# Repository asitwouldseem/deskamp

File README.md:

# deskamp
Class D amplifier / ESPHome pre-amp to match the custom speakers.

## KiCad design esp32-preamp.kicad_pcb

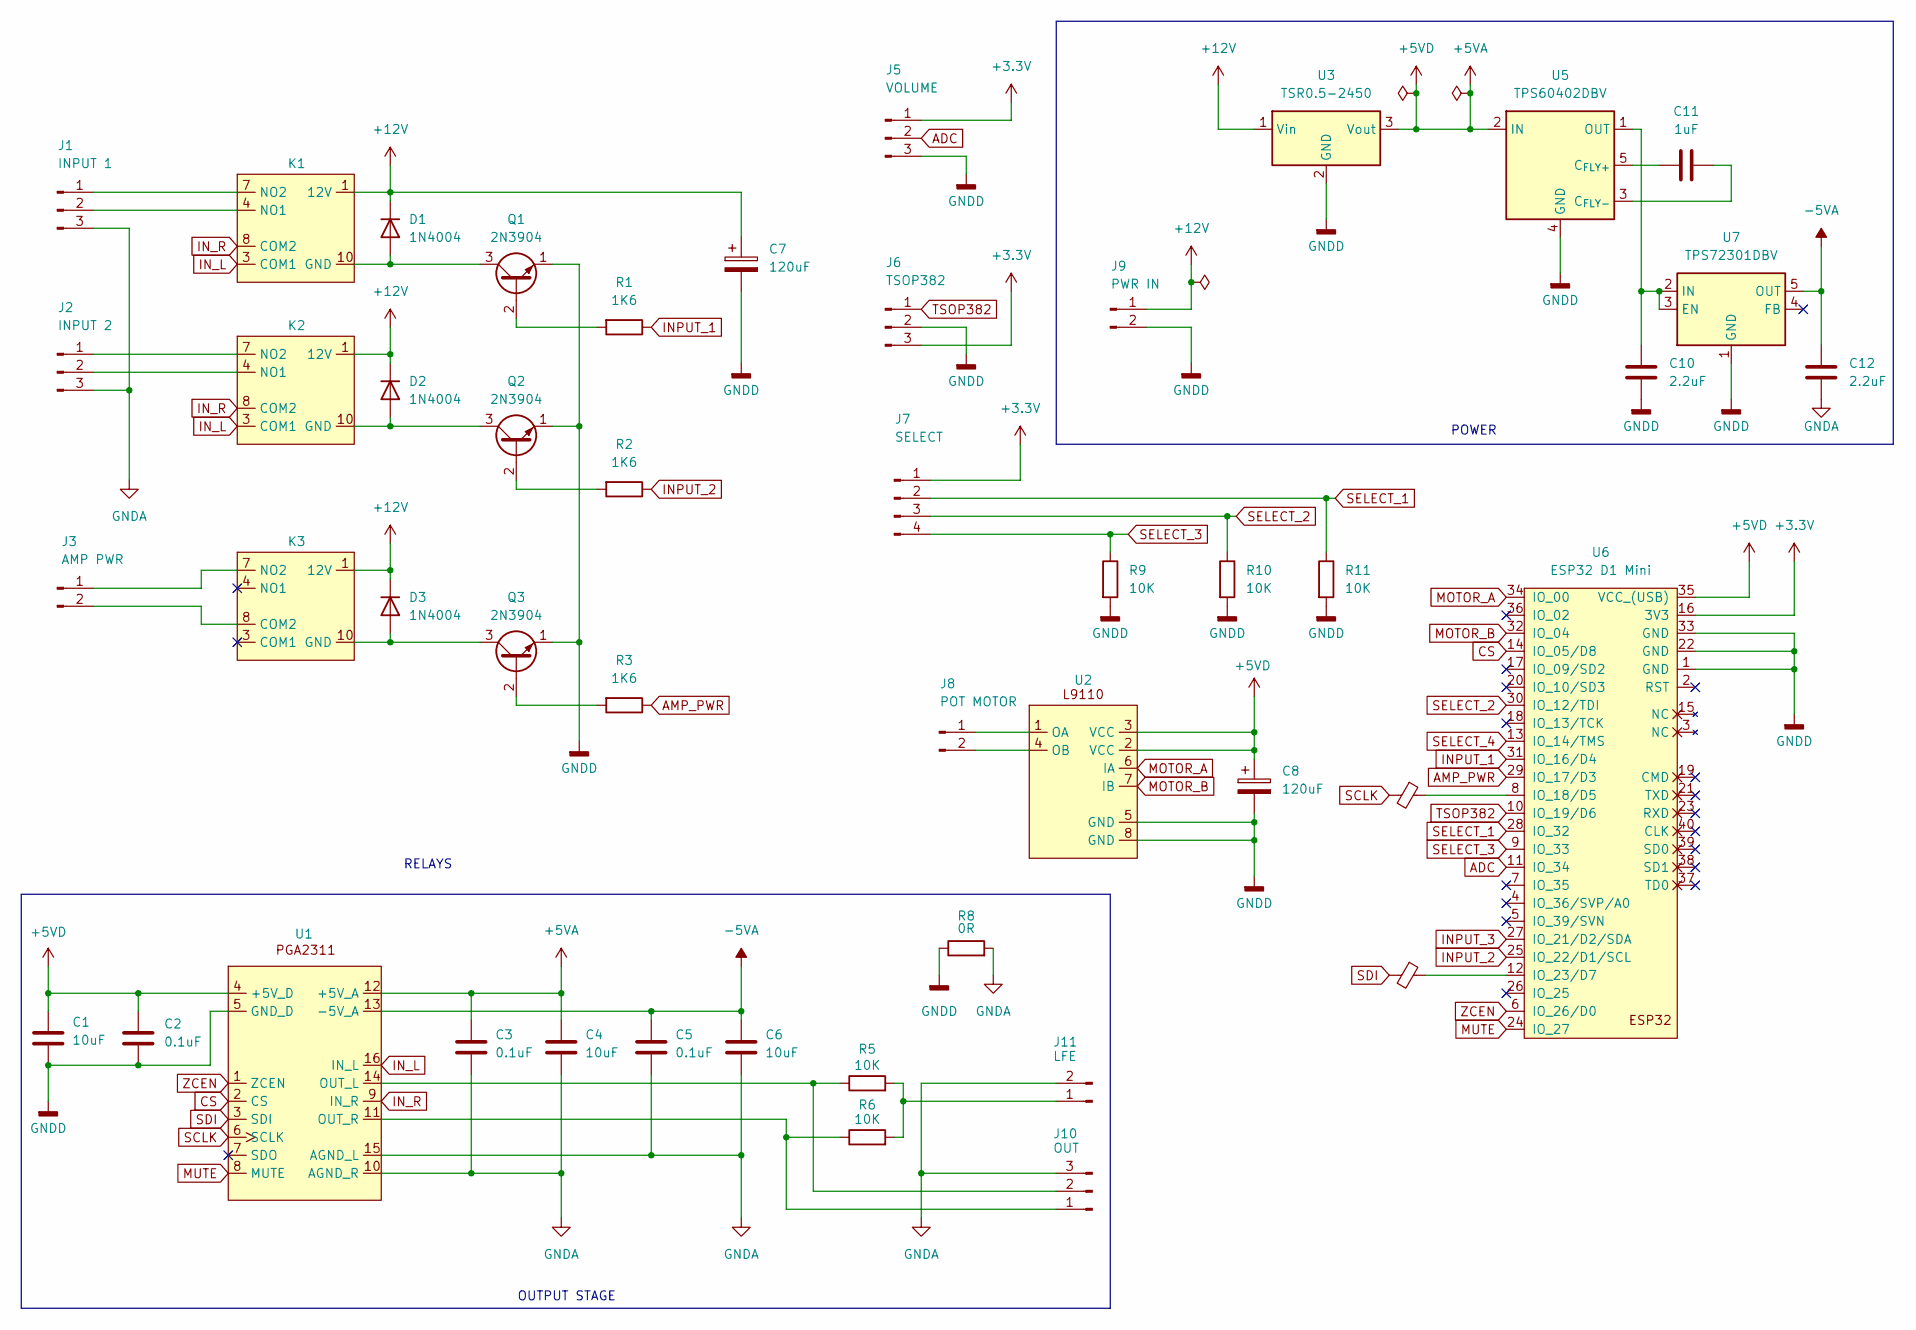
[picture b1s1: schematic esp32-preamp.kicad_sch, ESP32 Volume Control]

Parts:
C1, C4, C6: 10uF; C_Radial_D4.0mm_H5.0mm_P1.50mm
C2, C3, C5: 0.1uF; C_1206_3216Metric_Pad1.33x1.80mm_HandSolder
C7, C8: 120uF; C_Radial_D4.0mm_H5.0mm_P1.50mm
C10, C12: 2.2uF; C_1206_3216Metric_Pad1.33x1.80mm_HandSolder
C11: 1uF; C_1206_3216Metric_Pad1.33x1.80mm_HandSolder
D1, D2, D3: 1N4004; D_DO-41_SOD81_P10.16mm_Horizontal
FB1, FB2: FerriteBead_Small; C_1206_3216Metric_Pad1.33x1.80mm_HandSolder
J1: INPUT 1; JST_XH_B3B-XH-A_1x03_P2.50mm_Vertical
J2: INPUT 2; JST_XH_B3B-XH-A_1x03_P2.50mm_Vertical
J3: AMP PWR; JST_XH_B2B-XH-A_1x02_P2.50mm_Vertical
J5: VOLUME; JST_XH_B3B-XH-A_1x03_P2.50mm_Vertical
J6: TSOP382; JST_XH_B3B-XH-A_1x03_P2.50mm_Vertical
J7: SELECT; JST_XH_B4B-XH-A_1x04_P2.50mm_Vertical
J8: POT MOTOR; JST_XH_B2B-XH-A_1x02_P2.50mm_Vertical
J9: PWR IN; JST_XH_B2B-XH-A_1x02_P2.50mm_Vertical
J10: LFE; JST_XH_B2B-XH-A_1x02_P2.50mm_Vertical
J11: OUT; JST_XH_B3B-XH-A_1x03_P2.50mm_Vertical
K1, K2, K3: RELAY_TQ2_PAN
Q1, Q2, Q3: 2N3904; TO-92_Inline
R1, R2, R3: 1K6; R_1206_3216Metric_Pad1.30x1.75mm_HandSolder
R5, R6: 10K; R_Axial_Power_L30.0mm_W9.0mm_P36.4mm
R8: 0R; R_1206_3216Metric_Pad1.30x1.75mm_HandSolder
R9, R10, R11: 10K; R_1206_3216Metric_Pad1.30x1.75mm_HandSolder
U1: DW16
U2: DIP-8_W7.62mm_Socket
U3: TSR0.5-2450; Converter_DCDC_TRACO_TSR0.5-24xx_TSR0.5-24xxx_THT
U5: TPS60402DBV; SOT-23-5
U6: ESP32 D1 Mini; esp32-wemos-d1-mini
U7: TPS72301DBV; SOT-23-5

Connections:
+3.3V: J5.1, J6.3, J7.1, U6.16 (3V3)
+5VA: C1.1, C2.1, C3.1, C4.1, C8.1, U1.4 (+5V_D), U1.12 (+5V_A), U2.2 (VCC), U2.3 (VCC), U3.3 (Vout), U5.2 (IN), U6.35 (VCC_(USB))
+12V: C7.1, D1.1 (K), D2.1 (K), D3.1 (K), J9.1, K1.1 (12V), K2.1 (12V), K3.1 (12V), U3.1 (Vin)
-5VA: C5.1, C6.1, C12.1, U1.13 (-5V_A), U7.5 (OUT)
ADC: J5.2, U6.11 (IO_34)
AMP_PWR: R3.1, U6.29 (IO_17/D3)
CS: U1.2 (CS), U6.14 (IO_05/D8)
GNDA: C3.2, C4.2, C5.2, C6.2, C12.2, J1.3, J2.3, J10.2, J11.3, R8.2, U1.10 (AGND_R), U1.15 (AGND_L)
GNDD: C1.2, C2.2, C7.2, C8.2, C10.2, J5.3, J6.2, J9.2, Q1.1 (E), Q2.1 (E), Q3.1 (E), R8.1, R9.2, R10.2, R11.2, U1.5 (GND_D), U2.5 (GND), U2.8 (GND), U3.2 (GND), U5.4 (GND), U6.1 (GND), U6.22 (GND), U6.33 (GND), U7.1 (GND)
INPUT_1: R1.1, U6.31 (IO_16/D4)
INPUT_2: R2.1, U6.25 (IO_22/D1/SCL)
INPUT_3: U6.27 (IO_21/D2/SDA)
IN_L: K1.3 (COM1), K2.3 (COM1), U1.16 (IN_L)
IN_R: K1.8 (COM2), K2.8 (COM2), U1.9 (IN_R)
MOTOR_A: U2.6 (IA), U6.34 (IO_00)
MOTOR_B: U2.7 (IB), U6.32 (IO_04)
MUTE: U1.8 (MUTE), U6.24 (IO_27)
unnamed: D1.2 (A), K1.10 (GND), Q1.3 (C)
unnamed: D2.2 (A), K2.10 (GND), Q2.3 (C)
unnamed: D3.2 (A), K3.10 (GND), Q3.3 (C)
unnamed: J1.1, K1.7 (NO2)
unnamed: J1.2, K1.4 (NO1)
unnamed: J2.1, K2.7 (NO2)
unnamed: J2.2, K2.4 (NO1)
unnamed: J3.1, K3.7 (NO2)
unnamed: J3.2, K3.8 (COM2)
unnamed: J8.1, U2.1 (OA)
unnamed: J8.2, U2.4 (OB)
unnamed: J10.1, R5.2, R6.2
unnamed: J11.1, R6.1, U1.11 (OUT_R)
unnamed: J11.2, R5.1, U1.14 (OUT_L)
unnamed: Q1.2 (B), R1.2
unnamed: Q2.2 (B), R2.2
unnamed: Q3.2 (B), R3.2
unnamed: C11.1, U5.5 (C_{FLY+})
unnamed: C11.2, U5.3 (C_{FLY-})
unnamed: C10.1, U5.1 (OUT), U7.2 (IN), U7.3 (EN)
unnamed: FB1.1, U6.8 (IO_18/D5)
unnamed: FB2.1, U6.12 (IO_23/D7)
SCLK: FB1.2, U1.6 (SCLK)
SDI: FB2.2, U1.3 (SDI)
SELECT_1: J7.2, R11.1, U6.28 (IO_32)
SELECT_2: J7.3, R10.1, U6.30 (IO_12/TDI)
SELECT_3: J7.4, R9.1, U6.9 (IO_33)
SELECT_4: U6.13 (IO_14/TMS)
TSOP382: J6.1, U6.10 (IO_19/D6)
ZCEN: U1.1 (ZCEN), U6.6 (IO_26/D0)

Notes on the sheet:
OUTPUT STAGE
RELAYS
POWER

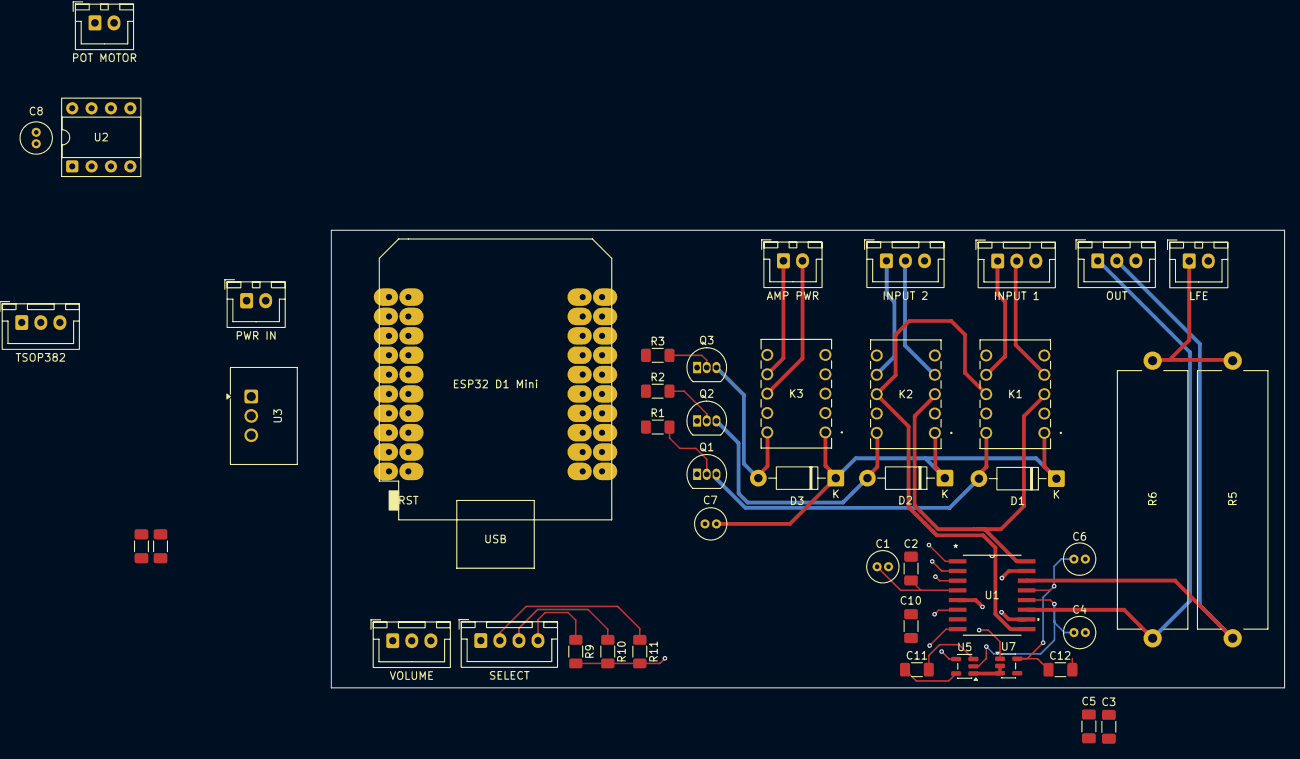
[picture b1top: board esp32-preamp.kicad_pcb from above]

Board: 2 copper layers, 125.0 x 60.0 mm, 47 parts (1 on the bottom side), 45 nets.

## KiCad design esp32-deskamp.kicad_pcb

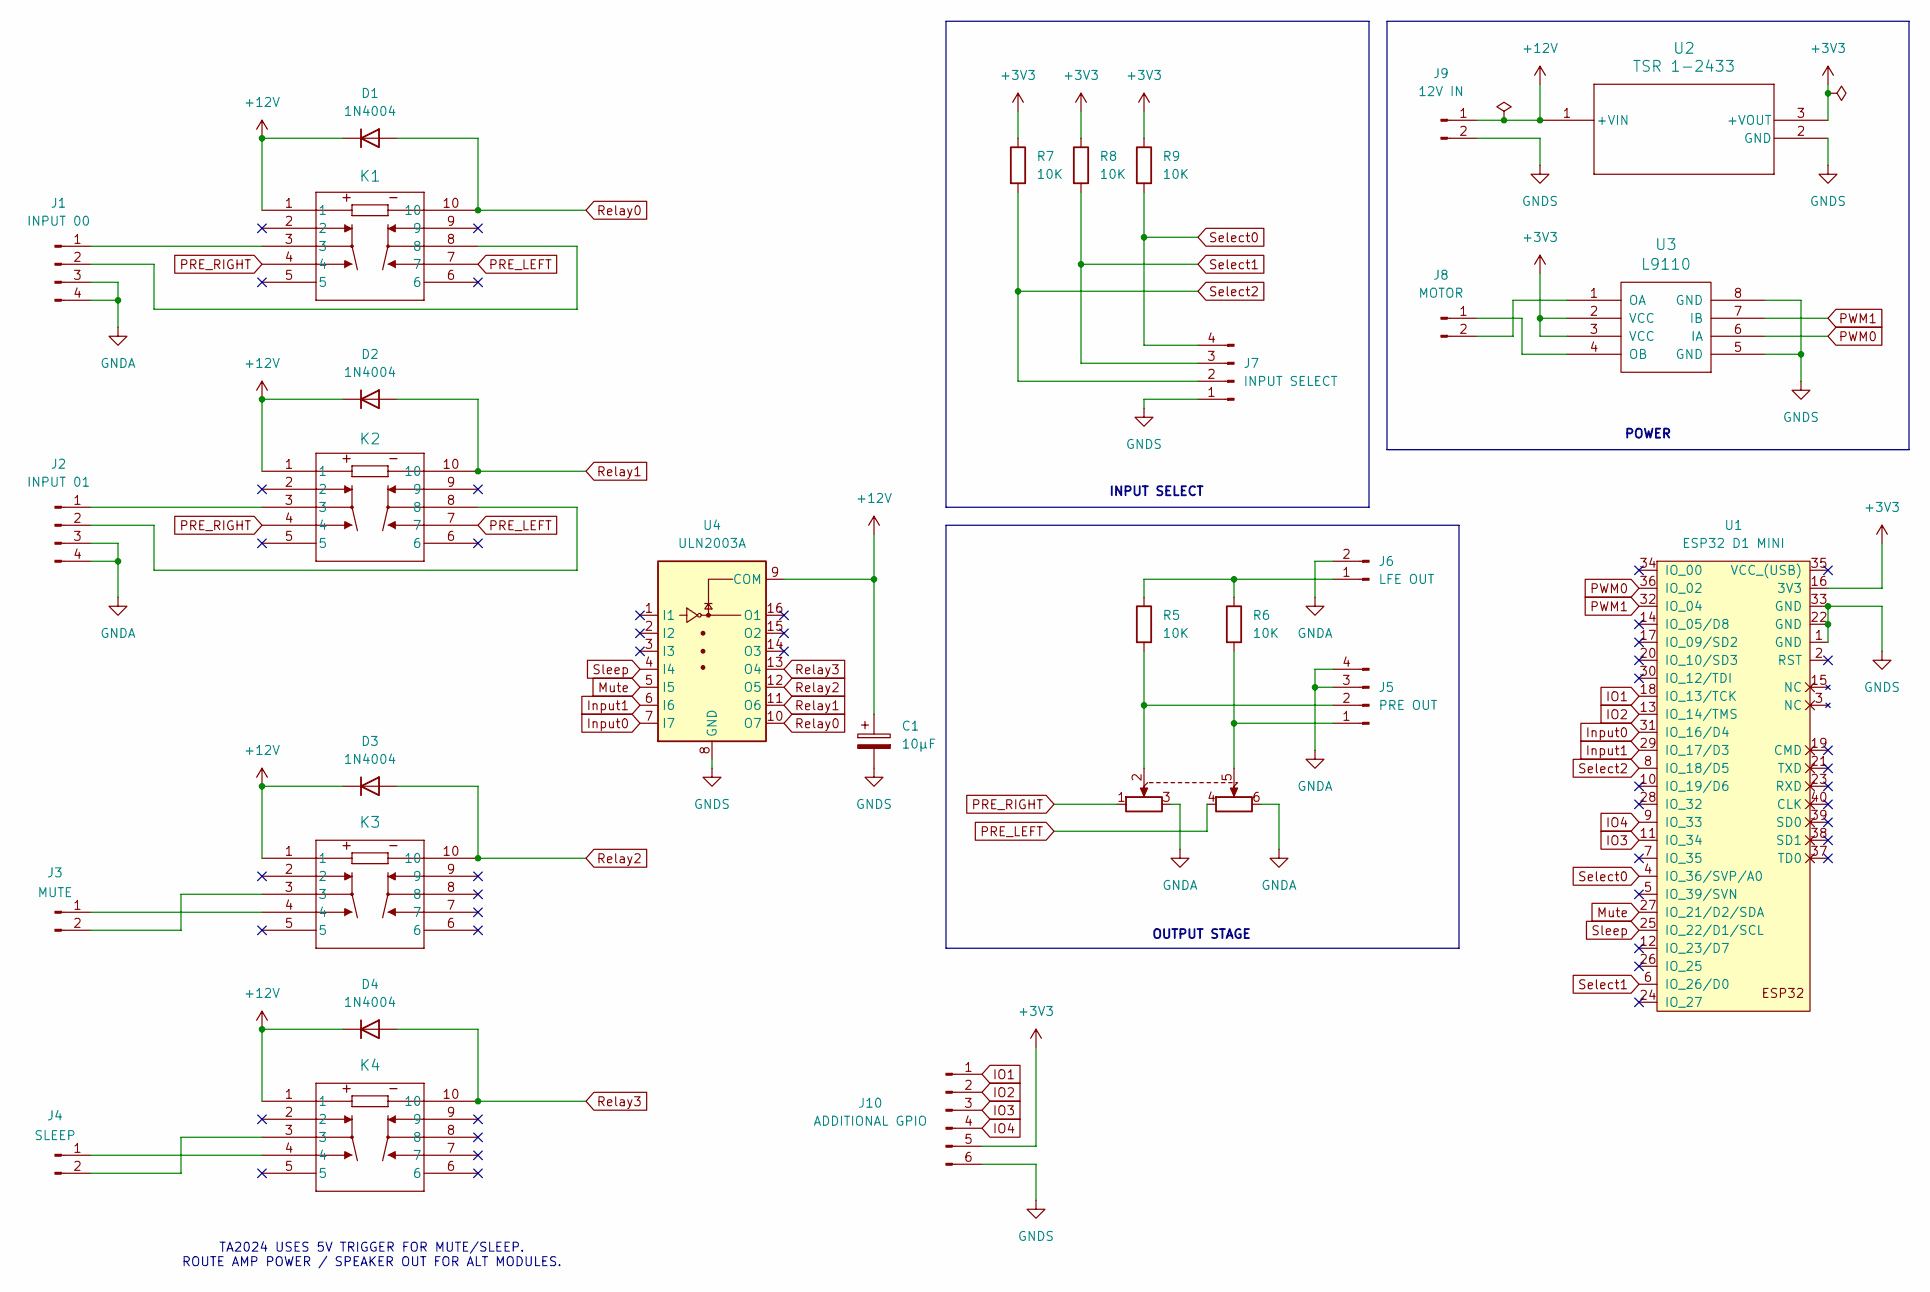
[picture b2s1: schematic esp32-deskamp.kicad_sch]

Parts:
C1: 10µF; CP_Radial_D5.0mm_P2.00mm
D1, D2, D3, D4: 1N4004; D_DO-35_SOD27_P7.62mm_Horizontal
J1: INPUT 00; JST_XH_B4B-XH-A_1x04_P2.50mm_Vertical
J2: INPUT 01; JST_XH_B4B-XH-A_1x04_P2.50mm_Vertical
J3: MUTE; JST_XH_B2B-XH-A_1x02_P2.50mm_Vertical
J4: SLEEP; JST_XH_B2B-XH-A_1x02_P2.50mm_Vertical
J5: PRE OUT; JST_XH_B4B-XH-A_1x04_P2.50mm_Vertical
J6: LFE OUT; JST_XH_B2B-XH-A_1x02_P2.50mm_Vertical
J7: INPUT SELECT; JST_XH_B4B-XH-A_1x04_P2.50mm_Vertical
J8: MOTOR; JST_XH_B2B-XH-A_1x02_P2.50mm_Vertical
J9: 12V IN; JST_XH_B2B-XH-A_1x02_P2.50mm_Vertical
J10: ADDITIONAL GPIO; PinHeader_1x06_P2.54mm_Vertical
K1: INPUT 00; RELAY_TQ2_PAN
K2: INPUT 01; RELAY_TQ2_PAN
K3: AMP MUTE; RELAY_TQ2_PAN
K4: AMP SLEEP; RELAY_TQ2_PAN
R5, R6: 10K; R_Axial_Power_L38.0mm_W9.0mm_P40.64mm
R7, R8, R9: 10K; R_Axial_DIN0204_L3.6mm_D1.6mm_P5.08mm_Horizontal
RV1: RK27112MC; Potentiometer_Alps_RK27112MC
U1: ESP32 D1 MINI; esp32-wemos-d1-mini
U2: TSR 1-2433; TSR1-SINGLE_TRP
U3: L9110; DIP-8_W7.62mm
U4: ULN2003A; DIP-16_W7.62mm

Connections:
+3V3: J10.5, R7.1, R8.1, R9.1, U1.16 (3V3), U2.3 (+VOUT), U3.2 (VCC), U3.3 (VCC)
+12V: C1.1, D1.1 (K), D2.1 (K), D3.1 (K), D4.1 (K), J9.1, K1.1, K2.1, K3.1, K4.1, U2.1 (+VIN), U4.9 (COM)
GNDA: J1.3, J1.4, J2.3, J2.4, J5.3, J5.4, J6.2, RV1.3, RV1.6
GNDS: C1.2, J7.1, J9.2, J10.6, U1.1 (GND), U1.22 (GND), U1.33 (GND), U2.2 (GND), U3.5 (GND), U3.8 (GND), U4.8 (GND)
IO1: J10.1, U1.18 (IO_13/TCK)
IO2: J10.2, U1.13 (IO_14/TMS)
IO3: J10.3, U1.11 (IO_34)
IO4: J10.4, U1.9 (IO_33)
Input0: U1.31 (IO_16/D4), U4.7 (I7)
Input1: U1.29 (IO_17/D3), U4.6 (I6)
Mute: U1.27 (IO_21/D2/SDA), U4.5 (I5)
unnamed: J1.1, K1.3
unnamed: J1.2, K1.8
unnamed: J2.1, K2.3
unnamed: J2.2, K2.8
unnamed: J3.1, K3.4
unnamed: J3.2, K3.3
unnamed: J4.1, K4.4
unnamed: J4.2, K4.3
unnamed: J5.1, R6.2, RV1.5
unnamed: J5.2, R5.2, RV1.2
unnamed: J6.1, R5.1, R6.1
unnamed: J8.1, U3.4 (OB)
unnamed: J8.2, U3.1 (OA)
PRE_LEFT: K1.7, K2.7, RV1.4
PRE_RIGHT: K1.4, K2.4, RV1.1
PWM0: U1.36 (IO_02), U3.6 (IA)
PWM1: U1.32 (IO_04), U3.7 (IB)
Relay0: D1.2 (A), K1.10, U4.10 (O7)
Relay1: D2.2 (A), K2.10, U4.11 (O6)
Relay2: D3.2 (A), K3.10, U4.12 (O5)
Relay3: D4.2 (A), K4.10, U4.13 (O4)
Select0: J7.4, R9.2, U1.4 (IO_36/SVP/A0)
Select1: J7.3, R8.2, U1.6 (IO_26/D0)
Select2: J7.2, R7.2, U1.8 (IO_18/D5)
Sleep: U1.25 (IO_22/D1/SCL), U4.4 (I4)

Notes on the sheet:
OUTPUT STAGE
INPUT SELECT
TA2024 USES 5V TRIGGER FOR MUTE/SLEEP. ROUTE AMP POWER / SPEAKER OUT FOR ALT MODULES.
POWER

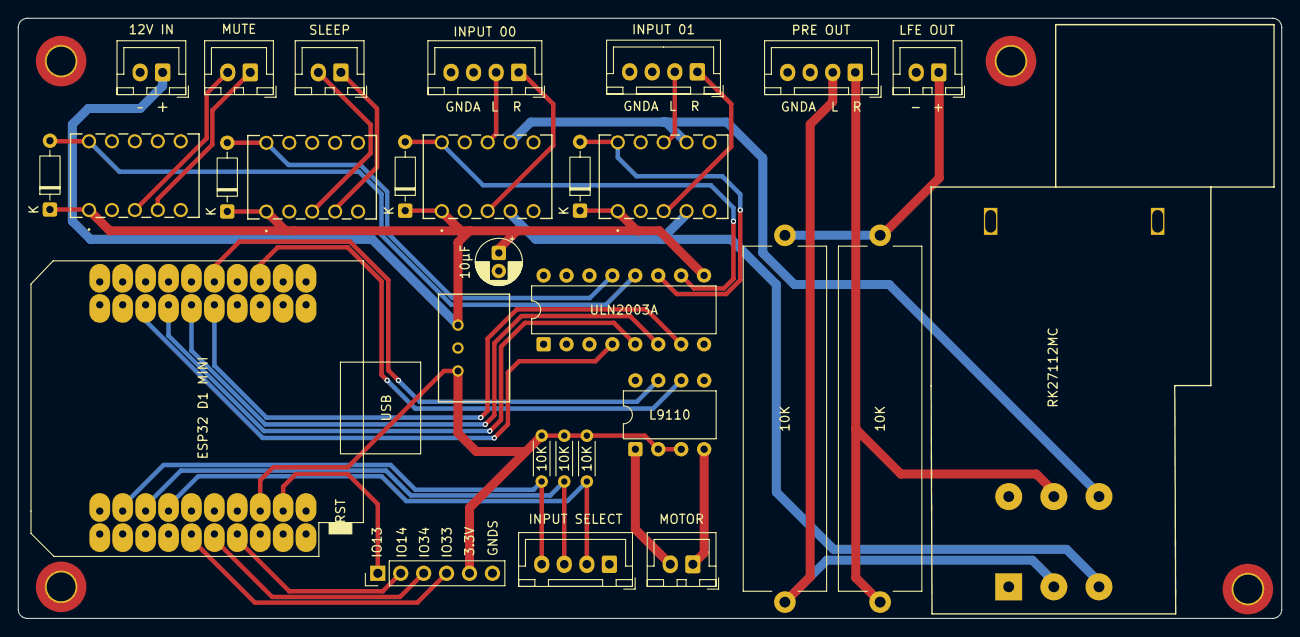
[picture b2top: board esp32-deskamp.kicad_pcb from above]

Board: 2 copper layers, 140.0 x 66.5 mm, 29 parts (0 on the bottom side), 36 nets.

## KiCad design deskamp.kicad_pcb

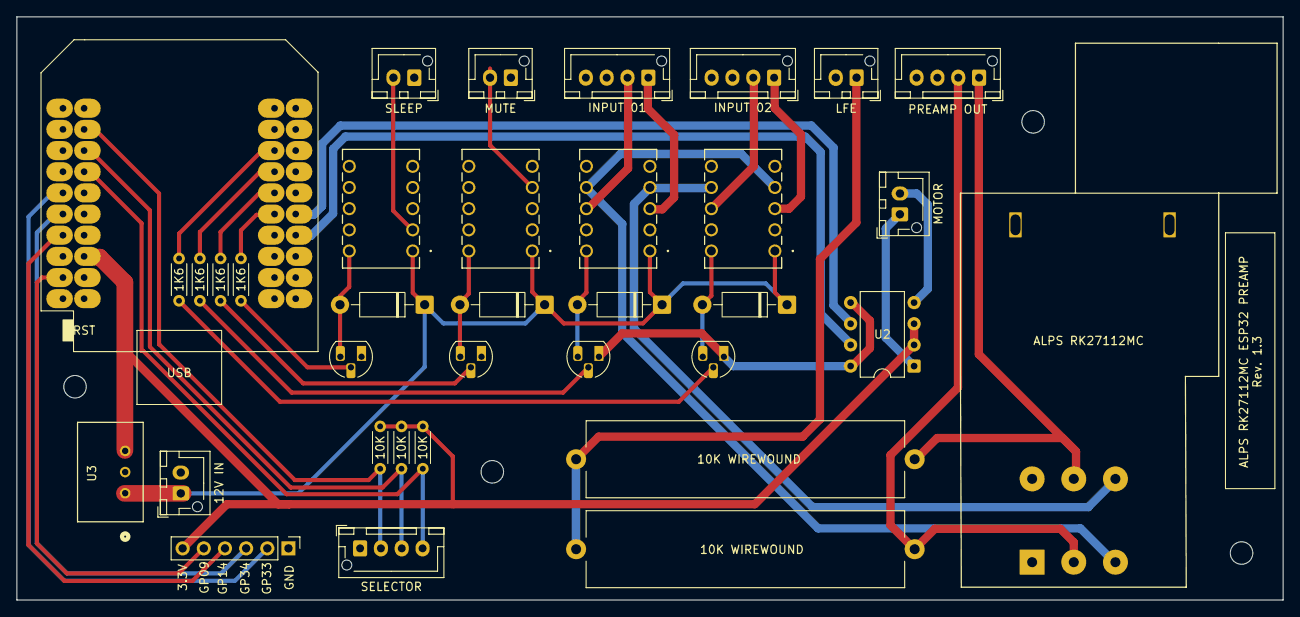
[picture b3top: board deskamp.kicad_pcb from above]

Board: 2 copper layers, 152.0 x 70.0 mm, 35 parts (0 on the bottom side), 38 nets.

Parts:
D1, D2, D3, D4: 1N4004; D_DO-41_SOD81_P10.16mm_Horizontal
J1: INPUT 01; JST_XH_B4B-XH-AM_1x04_P2.50mm_Vertical
J2: INPUT 02; JST_XH_B4B-XH-AM_1x04_P2.50mm_Vertical
J3: SLEEP; JST_XH_B2B-XH-AM_1x02_P2.50mm_Vertical
J4: MUTE; JST_XH_B2B-XH-AM_1x02_P2.50mm_Vertical
J5: PREAMP OUT; JST_XH_B4B-XH-AM_1x04_P2.50mm_Vertical
J6: LFE; JST_XH_B2B-XH-AM_1x02_P2.50mm_Vertical
J7: 12V IN; JST_XH_B2B-XH-AM_1x02_P2.50mm_Vertical
J8: MOTOR; JST_XH_B2B-XH-AM_1x02_P2.50mm_Vertical
J9: SELECTOR; JST_XH_B4B-XH-AM_1x04_P2.50mm_Vertical
J10: Extra GPIO; PinHeader_1x06_P2.54mm_Vertical
K1, K2, K3, K4: TQ2-12V; RELAY_TQ2_PAN
Q1, Q2, Q3, Q4: PN2222A; TO-92L_HandSolder
R1, R2, R3, R4: 1K6; R_Axial_DIN0204_L3.6mm_D1.6mm_P5.08mm_Horizontal
R5, R6: 10K; R_Axial_Power_L38.0mm_W9.0mm_P40.64mm
R7, R8, R9: 10K; R_Axial_DIN0204_L3.6mm_D1.6mm_P5.08mm_Horizontal
RV1: ALPS RK27; Potentiometer_Alps_RK27112MC
U1: esp32-wemos-d1-mini
U2: L9110; DIP-8_W7.62mm
U3: TSR_1-2433; TSR1-SINGLE_TRP

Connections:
+3V3: J10.6, R7.1, R8.1, R9.1, U1.16 (3V3), U2.2 (VCC), U2.3 (VCC), U3.3 (Vout)
+12V: D1.1 (K), D2.1 (K), D3.1 (K), D4.1 (K), J7.1, K1.1, K2.1, K3.1, K4.1, U3.1 (Vin)
GND: J3.1, J4.1, J7.2, J9.1, J10.1, K3.3, K4.3, Q1.1 (E), Q2.1 (E), Q3.1 (E), Q4.1 (E), U1.1 (GND), U1.22 (GND), U1.33 (GND), U2.5 (GND), U2.8 (GND), U3.2 (GND)
GNDA: J1.3, J1.4, J2.3, J2.4, J5.3, J5.4, J6.2, RV1.3, RV1.6
unnamed: D1.2 (A), K1.10, Q1.3 (C)
unnamed: D2.2 (A), K2.10, Q2.3 (C)
unnamed: D3.2 (A), K3.10, Q3.3 (C)
unnamed: D4.2 (A), K4.10, Q4.3 (C)
unnamed: J1.1, K1.3
unnamed: J1.2, K1.8
unnamed: J2.1, K2.3
unnamed: J2.2, K2.8
unnamed: J3.2, K3.2
unnamed: J4.2, K4.4
unnamed: J5.1, R6.2, RV1.5
unnamed: J5.2, R5.2, RV1.2
unnamed: J6.1, R5.1, R6.1
unnamed: J8.1, U2.1 (OA)
unnamed: J8.2, U2.4 (OB)
unnamed: J9.2, R9.2, U1.4 (IO_36/SVP/A0)
unnamed: J9.3, R8.2, U1.6 (IO_26/D0)
unnamed: J9.4, R7.2, U1.8 (IO_18/D5)
unnamed: J10.2, U1.9 (IO_33)
unnamed: J10.3, U1.11 (IO_34)
unnamed: J10.4, U1.13 (IO_14/TMS)
unnamed: J10.5, U1.17 (IO_09/SD2)
unnamed: K1.4, K2.7, RV1.4
unnamed: K1.7, K2.4, RV1.1
unnamed: Q1.2 (B), R1.1
unnamed: Q2.2 (B), R2.1
unnamed: Q3.2 (B), R3.1
unnamed: Q4.2 (B), R4.1
unnamed: U1.34 (IO_00), U2.7 (IB)
unnamed: U1.32 (IO_04), U2.6 (IA)
unnamed: R3.2, U1.31 (IO_16/D4)
unnamed: R4.2, U1.29 (IO_17/D3)
unnamed: R1.2, U1.27 (IO_21/D2/SDA)
unnamed: R2.2, U1.25 (IO_22/D1/SCL)

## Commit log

2025-10-03 Create project files
2025-10-03 Move out of sub directory
2025-10-03 Import ESP32 Mini lib
2025-10-05 Start building switch logic
2025-10-05 Start building frontend
2025-10-05 Fix flyback diodes, add amp relays
2025-10-05 Add potentiometer
2025-10-05 Add 3.3V regulator
2025-10-06 Add transistors, start building PCB
2025-10-06 Stuck until modelling Alps pot
2025-10-06 Use Alps RK27 as temp
2025-10-06 More arranging
2025-10-12 Add base resistors
2025-10-12 Fix footprints
2025-10-12 Check footprints
2025-10-12 Add rough pot footprint (first footprint!)
2025-10-12 Add NC tags to pass ERC
2025-10-12 Switch to 10K pulldown
2025-10-12 Layout stuff.
2025-10-12 Moar layout!
2025-10-12 Even more routing
2025-10-12 Change L9110 to Dip 8 footprint
2025-10-12 Run audio grounds
2025-10-12 Move pullup resistors
2025-10-12 Add 12V line for relays
2025-10-13 Start routing signals
2025-10-15 Add mute selector pulldown
2025-10-15 Update footprints
2025-10-17 Switch motor gpio for board layout
2025-10-18 Remove grounds in prep for ground plane
2025-10-18 Ready for ground plane
2025-10-18 Relocate pullup resistors
2025-10-18 Filled zones fun
2025-10-19 Add board edge
2025-11-01 Start afresh with layout
2025-11-02 Board layout
2025-11-02 Moar routing
2025-11-02 Route all but control
2025-11-02 Start edge cut
2025-11-02 Silkscreen fixes for DRC
2025-11-02 V1.1
2025-11-02 Update silkscreen
2025-11-08 Fix alignment, pending component test
2025-11-23 Add extra GPIO
2025-11-23 Remove U1 silkscreen
2025-11-23 Bump V1.2
2025-11-23 Fill grounds, bump to V1.3
2025-12-21 Simplify edge cut
2025-12-22 Switch to 2N3904
2026-01-01 Major refactor!
2026-01-01 Rebuild chunk of schematic
2026-01-01 Start routing, remove duplicate project
2026-01-01 Break time
2026-01-01 Locked in routing for relays
2026-01-03 Milestone, may tweak layout
2026-01-03 Enough for tonight, routed relay control board
2026-01-03 And a few other things
2026-01-03 Moar layout
2026-01-04 Fix cap footprint, moar layout
2026-01-04 Almost there, V3-something.
2026-01-04 IC routing
2026-01-04 No surprise, more routing (relays)
2026-01-11 Finish routing, start DRC
2026-01-11 Fix errors
2026-01-11 Move vias away from relay coils
2026-01-11 DRC checks
2026-01-11 Bump relays to 1mm track
2026-01-11 Name nets
2026-01-11 Move cap
2026-01-11 Resolve DRC warnings
2026-01-11 Fix edge cuts
2026-01-11 Change to proper µ symbol
2026-01-11 Create gerbers
2026-01-17 Tidy 3.3V
2026-05-10 Major refactor commence!
2026-05-10 Component selection (again)
2026-05-16 progress!
2026-05-16 Add motor circuit
2026-05-16 Repair duplicates
2026-05-16 Remove GNDS references
2026-05-16 Add jumper
2026-05-16 Prepare SDK lines
2026-05-17 Add more decoupling caps
2026-05-17 Add 120uF cap to motor driver
2026-05-17 Add ferrite beads
2026-05-17 Add regulators
2026-05-17 Tidy schematic
2026-05-17 Add caps on LDO
2026-05-20 Milestone
2026-05-21 Assign footprints
2026-05-21 Tidy footprints
2026-05-21 Fix R5/R6 footprint
2026-05-21 Group footprints
2026-05-31 Fix J7 to reflect two input preamp
2026-05-31 Move relay capacitor
2026-06-07 PGA2311
2026-06-22 More 5VA routing
2026-06-24 Tidy PGA2311 routing
